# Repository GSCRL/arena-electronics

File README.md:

# arena-electronics

# Other Repos

UI / Webserver - https://github.com/fubarlabs/RobotCombatOverlay
ESP32 Firmware - https://github.com/GSCRL/bot-arena-control
## Build Arg Notes

```ini
check_skip_packages = yes
lib_deps = bblanchon/ArduinoJson
build_flags = -O2 -D DEBUG_ESP_PORT=Serial
build_unflags = -Os
```

# Broker Setup

```
allow_anonymous true

listener 1883
protocol mqtt

listener 9001
protocol websockets
```

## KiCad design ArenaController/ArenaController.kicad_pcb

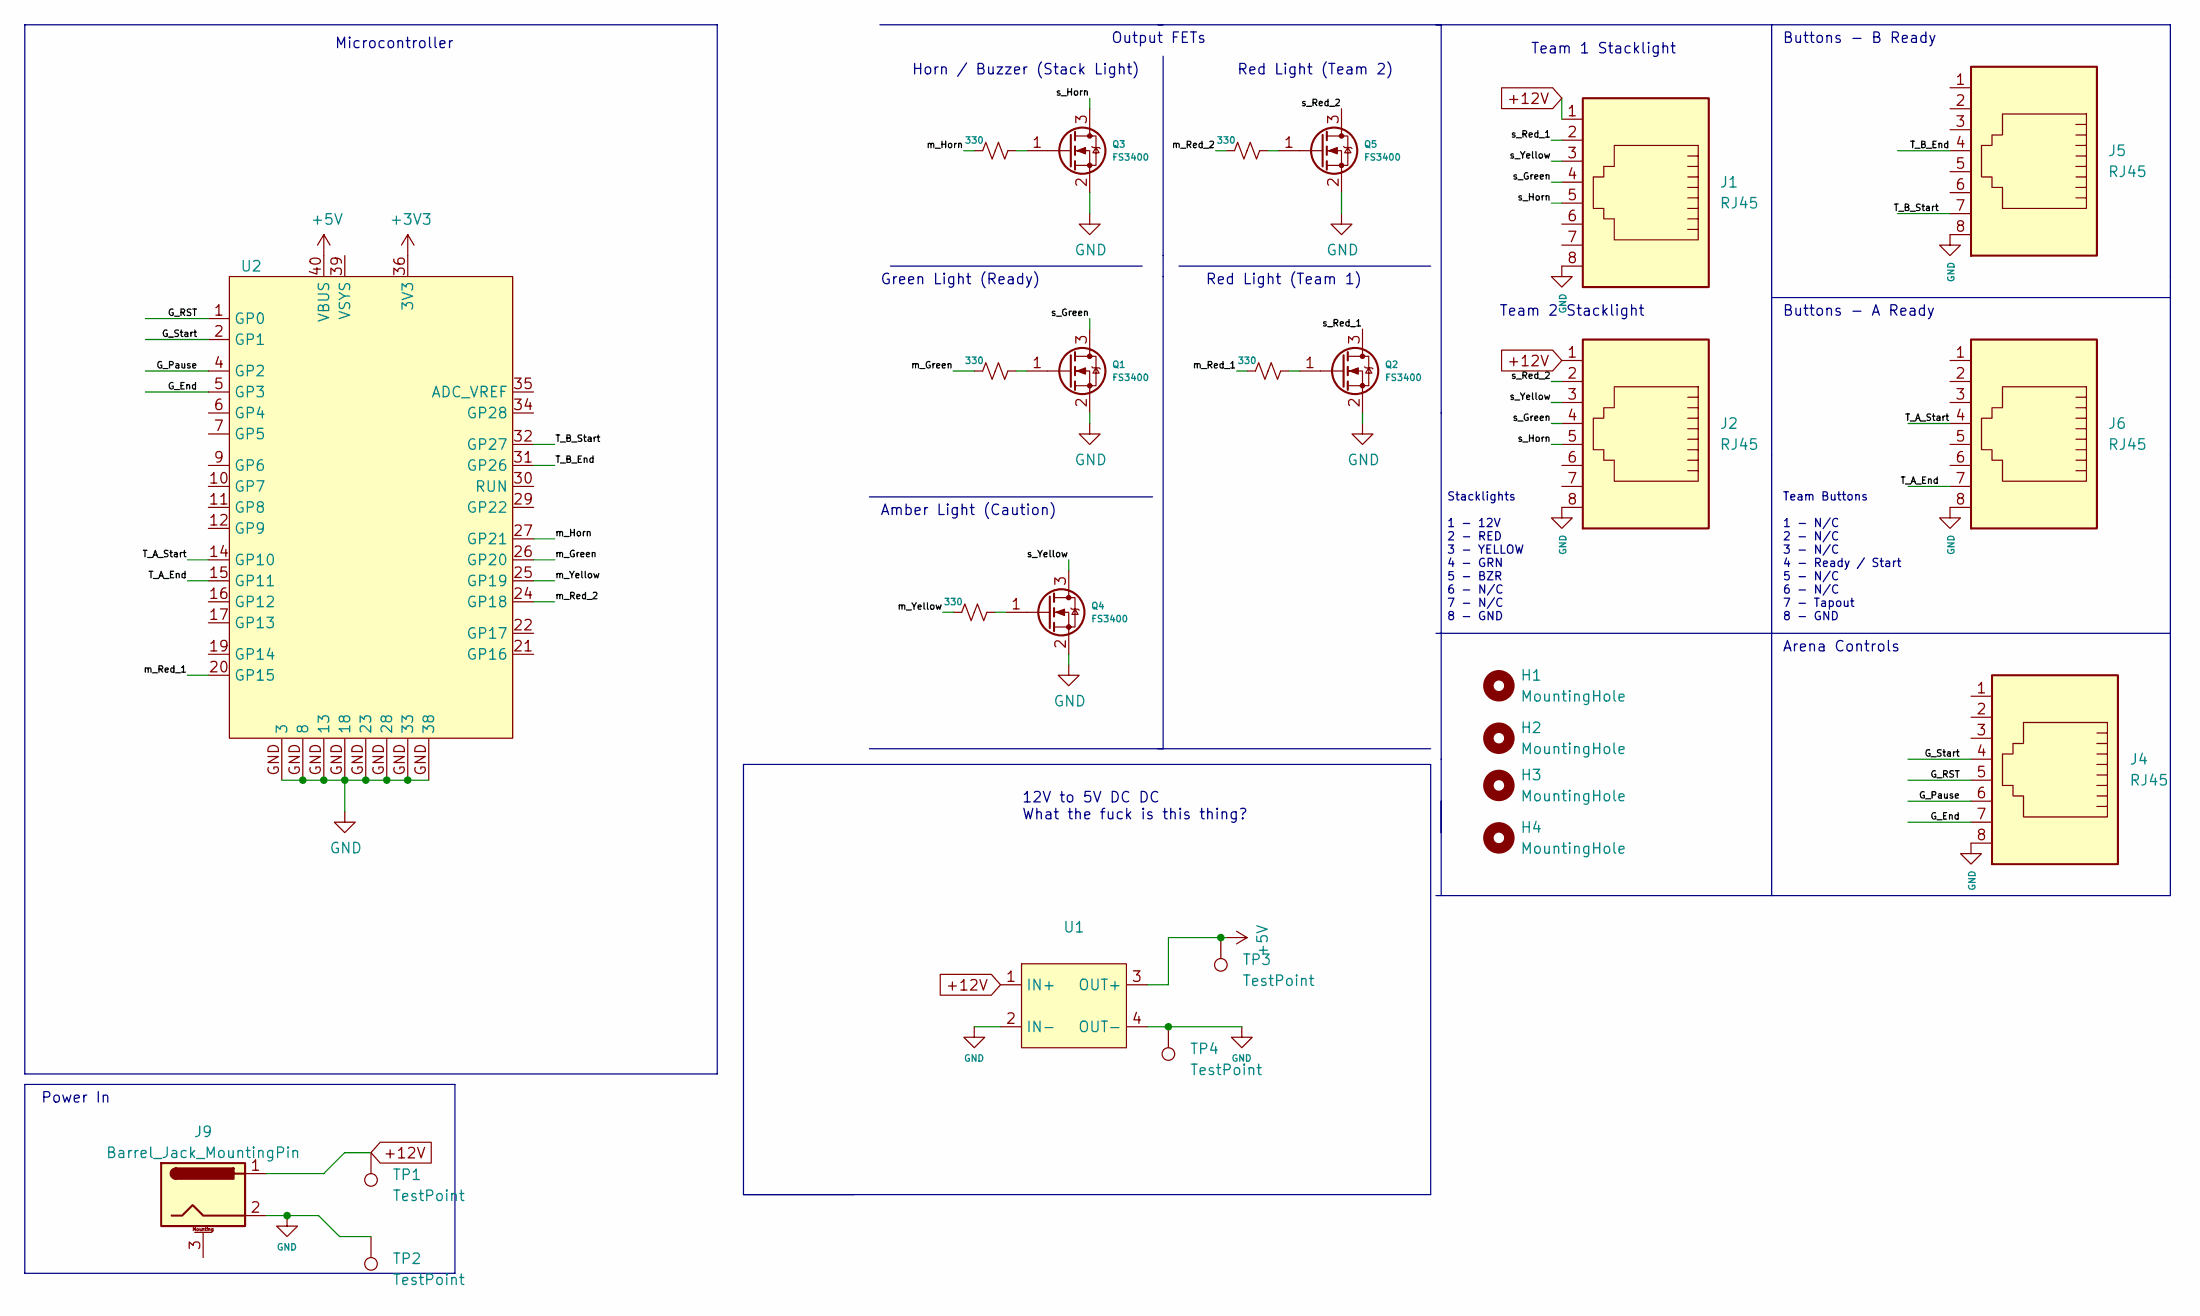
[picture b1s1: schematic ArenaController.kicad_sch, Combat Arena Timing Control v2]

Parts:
H1, H2, H3, H4: MountingHole; MountingHole_3.2mm_M3
J1, J2, J4, J5, J6: RJ45; RCH RC00139
J9: Barrel_Jack_MountingPin; BarrelJack_Horizontal
Q1, Q2, Q3, Q4, Q5: FS3400; SOT-23
R1, R2, R3, R4, R5: 330; R_1206_3216Metric_Pad1.30x1.75mm_HandSolder
TP1, TP2, TP3, TP4: TestPoint; TestPoint_Loop_D1.80mm_Drill1.0mm_Beaded
U1: LM2596_Module
U2: Raspberry_Pi_Pico_SMT_THT

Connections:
+3V3: U2.36 (3V3)
+5V: TP3.1, U1.3 (OUT+), U2.40 (VBUS)
+12V: J1.1, J2.1, J9.1, TP1.1, U1.1 (IN+)
/G_End: J4.7, U2.5 (GP3)
/G_Pause: J4.6, U2.4 (GP2)
/G_RST: J4.5, U2.1 (GP0)
/G_Start: J4.4, U2.2 (GP1)
/T_A_End: J6.7, U2.15 (GP11)
/T_A_Start: J6.4, U2.14 (GP10)
/T_B_End: J5.4, U2.31 (GP26)
/T_B_Start: J5.7, U2.32 (GP27)
/m_Green: R1.2, U2.26 (GP20)
/m_Horn: R2.2, U2.27 (GP21)
/m_Red_1: R5.2, U2.20 (GP15)
/m_Red_2: R4.2, U2.24 (GP18)
/m_Yellow: R3.2, U2.25 (GP19)
/s_Green: J1.4, J2.4, Q1.3 (D)
/s_Horn: J1.5, J2.5, Q3.3 (D)
/s_Red_1: J1.2, Q2.3 (D)
/s_Red_2: J2.2, Q5.3 (D)
/s_Yellow: J1.3, J2.3, Q4.3 (D)
GND: J1.8, J2.8, J4.8, J5.8, J6.8, J9.2, Q1.2 (S), Q2.2 (S), Q3.2 (S), Q4.2 (S), Q5.2 (S), TP2.1, TP4.1, U1.2 (IN-), U1.4 (OUT-), U2.GND (13)
unnamed: Q1.1 (G), R1.1
unnamed: Q2.1 (G), R5.1
unnamed: Q3.1 (G), R2.1
unnamed: Q4.1 (G), R3.1
unnamed: Q5.1 (G), R4.1

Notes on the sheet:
Amber Light (Caution)
Arena Controls
Microcontroller
Green Light (Ready)
Buttons - A Ready
Team 2 Stacklight
12V to 5V DC DC What the fuck is this thing?
Power In
Team 1 Stacklight
Output FETs
Horn / Buzzer (Stack Light)
Team Buttons 1 - N/C 2 - N/C 3 - N/C 4 - Ready / Start 5 - N/C 6 - N/C 7 - Tapout 8 - GND
Buttons - B Ready
Red Light (Team 1)
Red Light (Team 2)
Stacklights 1 - 12V 2 - RED 3 - YELLOW 4 - GRN 5 - BZR 6 - N/C 7 - N/C 8 - GND

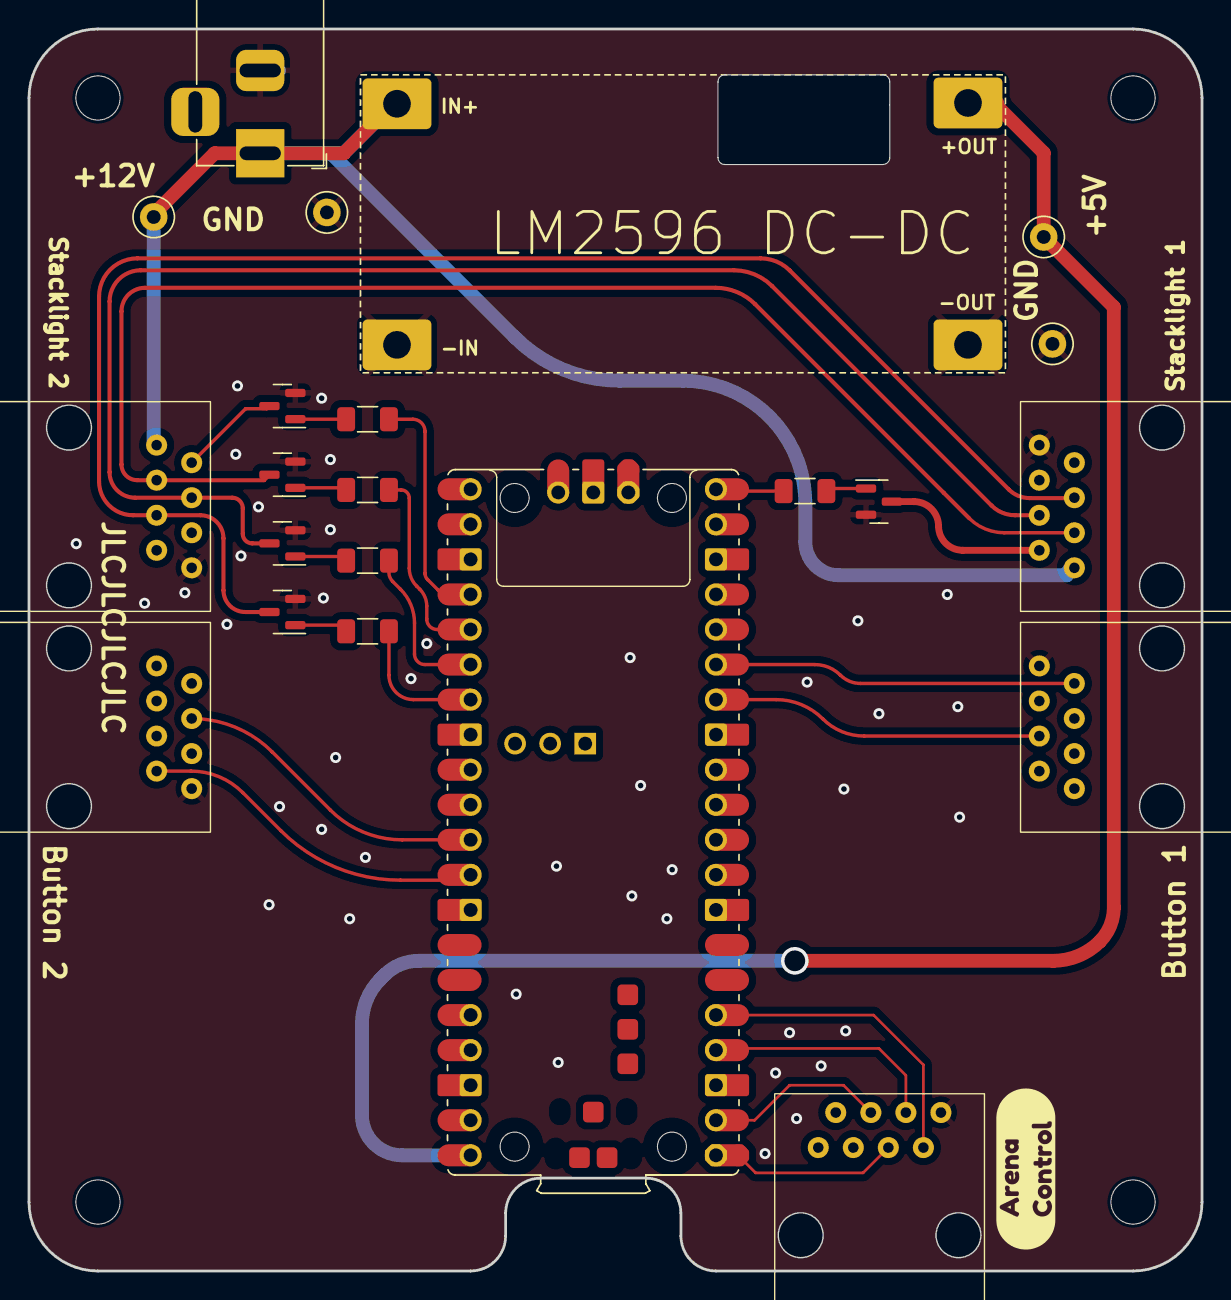
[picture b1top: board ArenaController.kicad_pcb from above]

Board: 2 copper layers, 85.0 x 90.0 mm, 27 parts (0 on the bottom side), 26 nets.

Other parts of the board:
kibuzzard-638A219C: G***; kibuzzard-638A219C

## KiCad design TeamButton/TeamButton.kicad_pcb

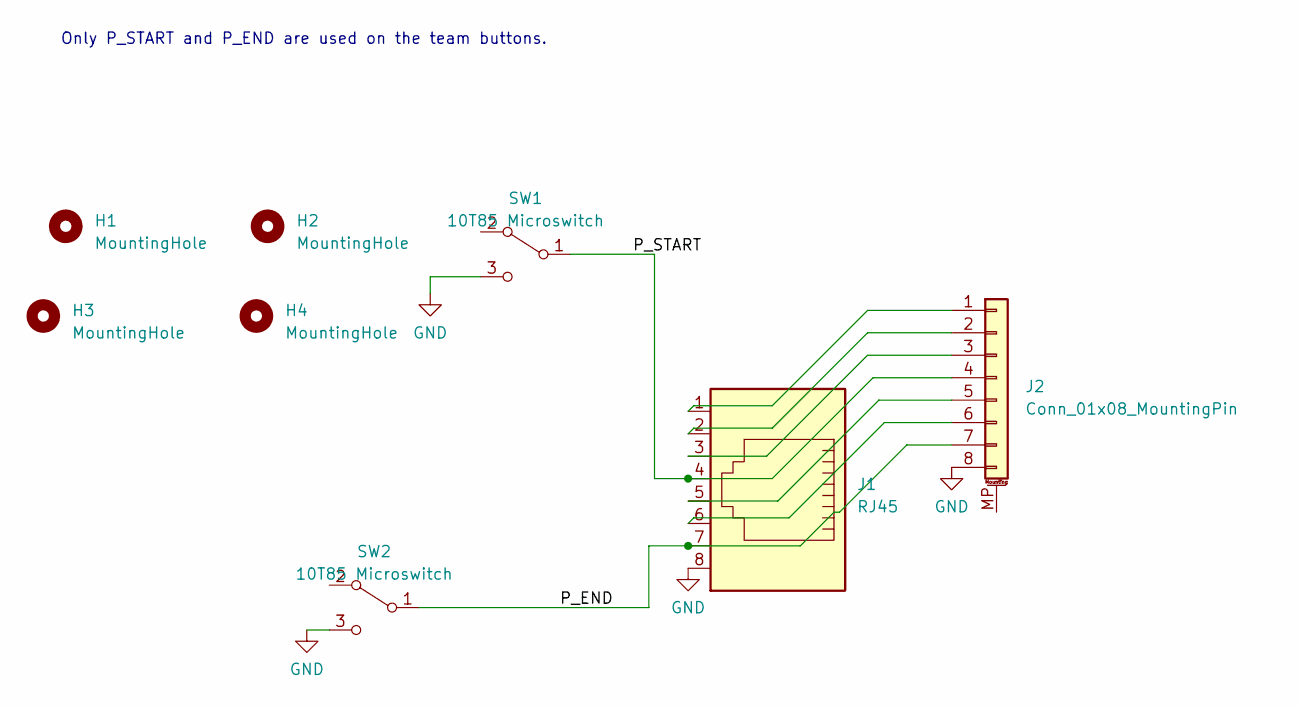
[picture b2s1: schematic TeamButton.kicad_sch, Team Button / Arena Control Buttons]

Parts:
H1, H2, H3, H4: MountingHole; MountingHole_3.2mm_M3
J1: RJ45; RCH RC00139
J2: Conn_01x08_MountingPin; PinSocket_1x08_P2.54mm_Horizontal
SW1, SW2: 10T85 Microswitch; 10T85 Microswitch with M3 mounts

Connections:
/P_END: J1.7, J2.7, SW2.1 (C)
/P_START: J1.4, J2.4, SW1.1 (C)
GND: J1.8, J2.8, SW1.3 (NO), SW2.3 (NO)
unnamed: J1.1, J2.1
unnamed: J1.2, J2.2
unnamed: J1.3, J2.3
unnamed: J1.5, J2.5
unnamed: J1.6, J2.6

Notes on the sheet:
Only P_START and P_END are used on the team buttons.

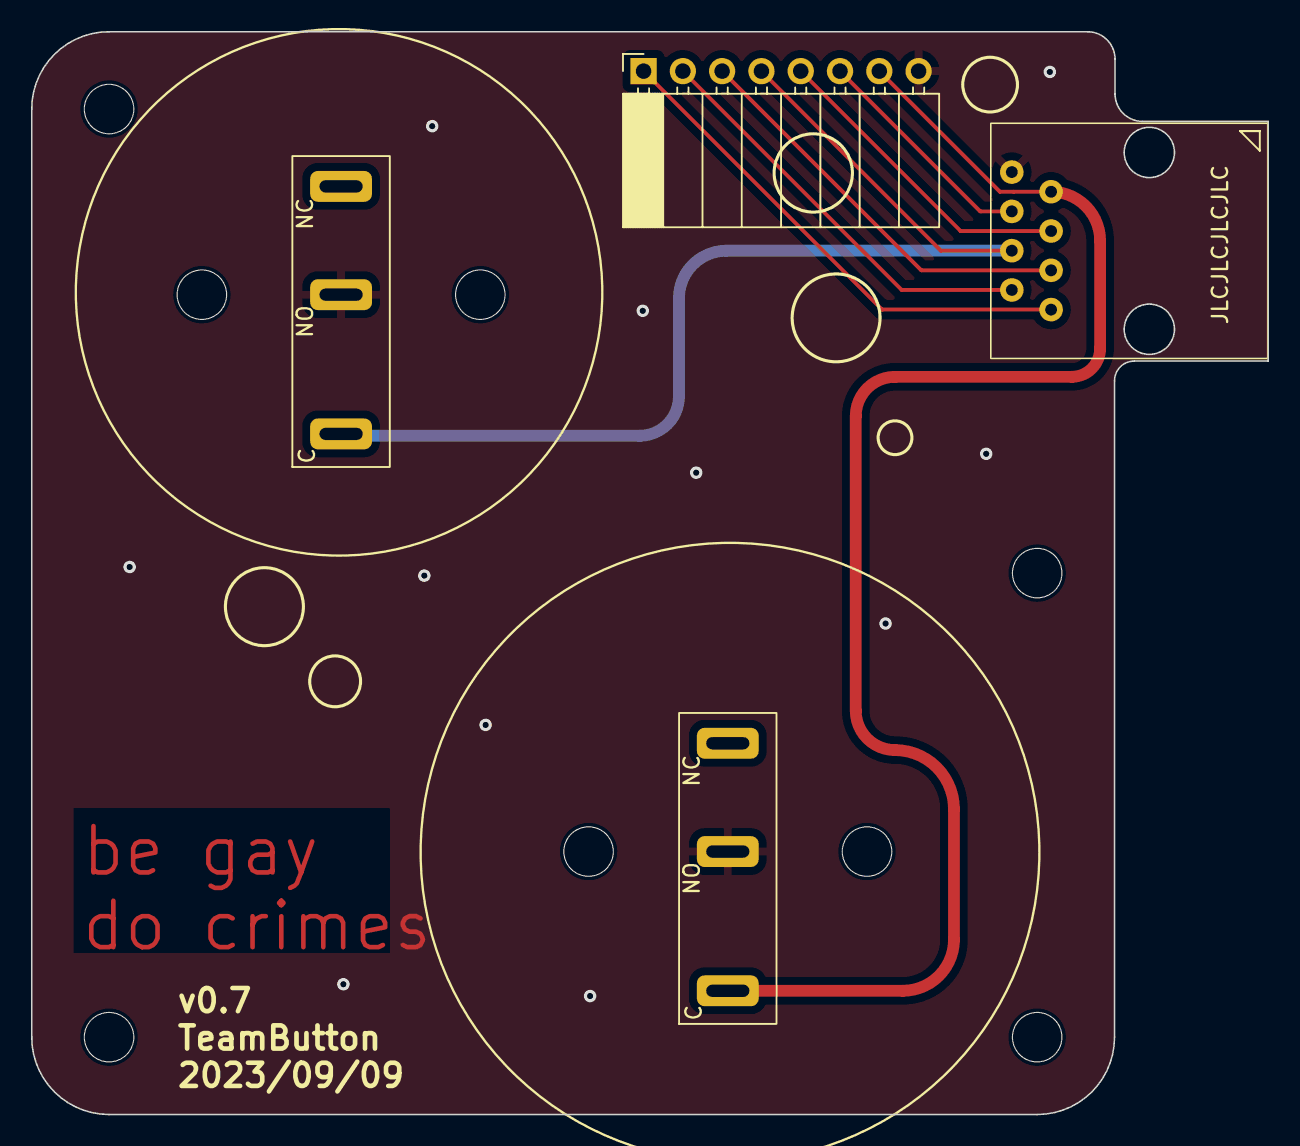
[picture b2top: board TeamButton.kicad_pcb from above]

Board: 2 copper layers, 79.9 x 70.0 mm, 8 parts (0 on the bottom side), 8 nets.

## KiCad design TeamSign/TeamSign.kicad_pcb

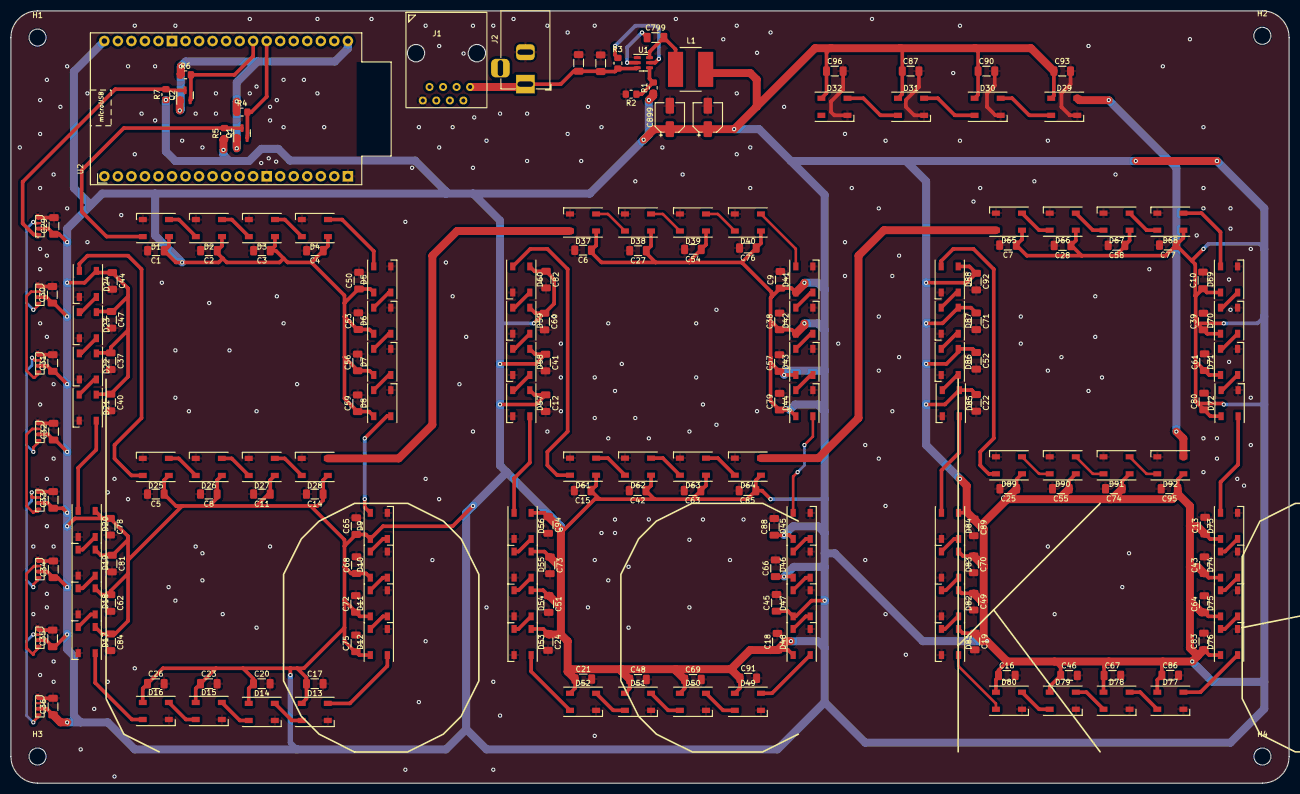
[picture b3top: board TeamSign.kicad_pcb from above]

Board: 2 copper layers, 240.0 x 145.0 mm, 215 parts (0 on the bottom side), 106 nets.

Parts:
C1, C2, C3, C4, C5, C6, C7, C8, C9, C10, C11, C12, C13, C14, C15, C16, C17, C18, C19, C20, C21, C22, C23, C24, C25, C26, C27, C28, C29, C30, C31, C32, C33, C34, C35, C36, C37, C38, C39, C40, C41, C42, C43, C44, C45, C46, C47, C48, C49, C50, C51, C52, C53, C54, C55, C56, C57, C58, C59, C60, C61, C62, C63, C64, C65, C66, C67, C68, C69, C70, C71, C72, C73, C74, C75, C76, C77, C78, C79, C80, C81, C82, C83, C84, C85, C86, C87, C88, C89, C90, C91, C92, C93, C94, C95, C96, C799: 100nF; C_1206_3216Metric_Pad1.33x1.80mm_HandSolder
C898, C899: 22uF; CP_Elec_5x5.4
C998, C999: 10uF; C_1206_3216Metric_Pad1.33x1.80mm_HandSolder
D1, D2, D3, D4, D5, D6, D7, D8, D9, D10, D11, D12, D13, D14, D15, D16, D17, D18, D19, D20, D21, D22, D23, D24, D25, D26, D27, D28, D29, D30, D31, D32, D37, D38, D39, D40, D41, D42, D43, D44, D45, D46, D47, D48, D49, D50, D51, D52, D53, D54, D55, D56, D57, D58, D59, D60, D61, D62, D63, D64, D65, D66, D67, D68, D69, D70, D71, D72, D73, D74, D75, D76, D77, D78, D79, D80, D81, D82, D83, D84, D85, D86, D87, D88, D89, D90, D91, D92: SK6812; LED_SK6812_PLCC4_5.0x5.0mm_P3.2mm
D300, D301, D302, D303, D304, D305, D306, D307: SK6812-Side-A
H1, H2, H3, H4: MountingHole; MountingHole_3.2mm_M3
J1: RJ45; RCH RC00139
J2: Barrel_Jack_MountingPin; BarrelJack_Horizontal
L1: 3.3uH; L_Bourns_SRN8040TA
Q1, Q2: BSS138; SOT-23
R1: 54.9kΩ; R_0805_2012Metric_Pad1.20x1.40mm_HandSolder
R2, R3, R4, R5, R6, R7: 10kΩ; R_0805_2012Metric_Pad1.20x1.40mm_HandSolder
U1: TPS563200; SOT-23-6
U2: ESP32-Devkit_C_V4; MODULE_ESP32_DEVKIT_C_V4

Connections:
+3.3V: Q1.1 (G), Q2.1 (G), R4.1, R6.1, U2.20 (3.3v)
+5V: C1.1, C2.1, C3.1, C4.1, C5.1, C6.1, C7.1, C8.1, C9.1, C10.1, C11.1, C12.1, C13.1, C14.1, C15.1, C16.1, C17.1, C18.1, C19.1, C20.1, C21.1, C22.1, C23.1, C24.1, C25.1, C26.1, C27.1, C28.1, C29.1, C30.1, C31.1, C32.1, C33.1, C34.1, C35.1, C36.1, C37.1, C38.1, C39.1, C40.1, C41.1, C42.1, C43.1, C44.1, C45.1, C46.1, C47.1, C48.1, C49.1, C50.1, C51.1, C52.1, C53.1, C54.1, C55.1, C56.1, C57.1, C58.1, C59.1, C60.1, C61.1, C62.1, C63.1, C64.1, C65.1, C66.1, C67.1, C68.1, C69.1, C70.1, C71.1, C72.1, C73.1, C74.1, C75.1, C76.1, C77.1, C78.1, C79.1, C80.1, C81.1, C82.1, C83.1, C84.1, C85.1, C86.1, C87.1, C88.1, C89.1, C90.1, C91.1, C92.1, C93.1, C94.1, C95.1, C96.1, C898.1, C899.1, D1.3 (VDD), D2.3 (VDD), D3.3 (VDD), D4.3 (VDD), D5.3 (VDD), D6.3 (VDD), D7.3 (VDD), D8.3 (VDD), D9.3 (VDD), D10.3 (VDD), D11.3 (VDD), D12.3 (VDD), D13.3 (VDD), D14.3 (VDD), D15.3 (VDD), D16.3 (VDD), D17.3 (VDD), D18.3 (VDD), D19.3 (VDD), D20.3 (VDD), D21.3 (VDD), D22.3 (VDD), D23.3 (VDD), D24.3 (VDD), D25.3 (VDD), D26.3 (VDD), D27.3 (VDD), D28.3 (VDD), D29.3 (VDD), D30.3 (VDD), D31.3 (VDD), D32.3 (VDD), D37.3 (VDD), D38.3 (VDD), D39.3 (VDD), D40.3 (VDD), D41.3 (VDD), D42.3 (VDD), D43.3 (VDD), D44.3 (VDD), D45.3 (VDD), D46.3 (VDD), D47.3 (VDD), D48.3 (VDD), D49.3 (VDD), D50.3 (VDD), D51.3 (VDD), D52.3 (VDD), D53.3 (VDD), D54.3 (VDD), D55.3 (VDD), D56.3 (VDD), D57.3 (VDD), D58.3 (VDD), D59.3 (VDD), D60.3 (VDD), D61.3 (VDD), D62.3 (VDD), D63.3 (VDD), D64.3 (VDD), D65.3 (VDD), D66.3 (VDD), D67.3 (VDD), D68.3 (VDD), D69.3 (VDD), D70.3 (VDD), D71.3 (VDD), D72.3 (VDD), D73.3 (VDD), D74.3 (VDD), D75.3 (VDD), D76.3 (VDD), D77.3 (VDD), D78.3 (VDD), D79.3 (VDD), D80.3 (VDD), D81.3 (VDD), D82.3 (VDD), D83.3 (VDD), D84.3 (VDD), D85.3 (VDD), D86.3 (VDD), D87.3 (VDD), D88.3 (VDD), D89.3 (VDD), D90.3 (VDD), D91.3 (VDD), D92.3 (VDD), D300.2 (VDD), D301.2 (VDD), D302.2 (VDD), D303.2 (VDD), D304.2 (VDD), D305.2 (VDD), D306.2 (VDD), D307.2 (VDD), L1.2, R1.1, R5.1, R7.1, U2.38 (5V)
+12V: C998.1, C999.1, J1.1, J2.1, R3.1, U1.3 (VIN)
/LED Array 1/sk_output_pin: D28.4 (DOUT), D37.2 (DIN)
/LED Array 1/sk_pin1: D12.4 (DOUT), D13.2 (DIN)
/LED Array 1/sk_pin2: D25.4 (DOUT), D26.2 (DIN)
/LED Array 2/sk_output_pin: D64.4 (DOUT), D65.2 (DIN)
/LED Array 2/sk_pin1: D48.4 (DOUT), D49.2 (DIN)
/LED Array 2/sk_pin2: D61.4 (DOUT), D62.2 (DIN)
/LED Array 3/sk_pin1: D76.4 (DOUT), D77.2 (DIN)
/LED Array 3/sk_pin2: D89.4 (DOUT), D90.2 (DIN)
/led_output_frontfiring: D29.2 (DIN), D92.4 (DOUT)
/sk_input: Q1.2 (S), R4.2, U2.26 (RTC_GPIO9/XTal32P/Touch9/ADC1_4/GPIO32)
/sk_lvl_shifted: D1.2 (DIN), Q1.3 (D), R5.2
/stacklight_lvl_shift: D300.1 (DIN), Q2.3 (D), R7.2
/stacklight_out: Q2.2 (S), R6.2, U2.27 (RTC_GPIO8/Xtal32N/Touch8/ADC1_5/GPIO33)
GND: C1.2, C2.2, C3.2, C4.2, C5.2, C6.2, C7.2, C8.2, C9.2, C10.2, C11.2, C12.2, C13.2, C14.2, C15.2, C16.2, C17.2, C18.2, C19.2, C20.2, C21.2, C22.2, C23.2, C24.2, C25.2, C26.2, C27.2, C28.2, C29.2, C30.2, C31.2, C32.2, C33.2, C34.2, C35.2, C36.2, C37.2, C38.2, C39.2, C40.2, C41.2, C42.2, C43.2, C44.2, C45.2, C46.2, C47.2, C48.2, C49.2, C50.2, C51.2, C52.2, C53.2, C54.2, C55.2, C56.2, C57.2, C58.2, C59.2, C60.2, C61.2, C62.2, C63.2, C64.2, C65.2, C66.2, C67.2, C68.2, C69.2, C70.2, C71.2, C72.2, C73.2, C74.2, C75.2, C76.2, C77.2, C78.2, C79.2, C80.2, C81.2, C82.2, C83.2, C84.2, C85.2, C86.2, C87.2, C88.2, C89.2, C90.2, C91.2, C92.2, C93.2, C94.2, C95.2, C96.2, C898.2, C899.2, C998.2, C999.2, D1.1 (VSS), D2.1 (VSS), D3.1 (VSS), D4.1 (VSS), D5.1 (VSS), D6.1 (VSS), D7.1 (VSS), D8.1 (VSS), D9.1 (VSS), D10.1 (VSS), D11.1 (VSS), D12.1 (VSS), D13.1 (VSS), D14.1 (VSS), D15.1 (VSS), D16.1 (VSS), D17.1 (VSS), D18.1 (VSS), D19.1 (VSS), D20.1 (VSS), D21.1 (VSS), D22.1 (VSS), D23.1 (VSS), D24.1 (VSS), D25.1 (VSS), D26.1 (VSS), D27.1 (VSS), D28.1 (VSS), D29.1 (VSS), D30.1 (VSS), D31.1 (VSS), D32.1 (VSS), D37.1 (VSS), D38.1 (VSS), D39.1 (VSS), D40.1 (VSS), D41.1 (VSS), D42.1 (VSS), D43.1 (VSS), D44.1 (VSS), D45.1 (VSS), D46.1 (VSS), D47.1 (VSS), D48.1 (VSS), D49.1 (VSS), D50.1 (VSS), D51.1 (VSS), D52.1 (VSS), D53.1 (VSS), D54.1 (VSS), D55.1 (VSS), D56.1 (VSS), D57.1 (VSS), D58.1 (VSS), D59.1 (VSS), D60.1 (VSS), D61.1 (VSS), D62.1 (VSS), D63.1 (VSS), D64.1 (VSS), D65.1 (VSS), D66.1 (VSS), D67.1 (VSS), D68.1 (VSS), D69.1 (VSS), D70.1 (VSS), D71.1 (VSS), D72.1 (VSS), D73.1 (VSS), D74.1 (VSS), D75.1 (VSS), D76.1 (VSS), D77.1 (VSS), D78.1 (VSS), D79.1 (VSS), D80.1 (VSS), D81.1 (VSS), D82.1 (VSS), D83.1 (VSS), D84.1 (VSS), D85.1 (VSS), D86.1 (VSS), D87.1 (VSS), D88.1 (VSS), D89.1 (VSS), D90.1 (VSS), D91.1 (VSS), D92.1 (VSS), D300.4 (GND), D301.4 (GND), D302.4 (GND), D303.4 (GND), D304.4 (GND), D305.4 (GND), D306.4 (GND), D307.4 (GND), J1.8, J2.2, R2.2, U1.1 (GND), U2.13 (GND), U2.19 (GND), U2.33 (GND)
unnamed: D1.4 (DOUT), D2.2 (DIN)
unnamed: D2.4 (DOUT), D3.2 (DIN)
unnamed: D3.4 (DOUT), D4.2 (DIN)
unnamed: D4.4 (DOUT), D5.2 (DIN)
unnamed: D5.4 (DOUT), D6.2 (DIN)
unnamed: D6.4 (DOUT), D7.2 (DIN)
unnamed: D7.4 (DOUT), D8.2 (DIN)
unnamed: D8.4 (DOUT), D9.2 (DIN)
unnamed: D9.4 (DOUT), D10.2 (DIN)
unnamed: D10.4 (DOUT), D11.2 (DIN)
unnamed: D11.4 (DOUT), D12.2 (DIN)
unnamed: D13.4 (DOUT), D14.2 (DIN)
unnamed: D14.4 (DOUT), D15.2 (DIN)
unnamed: D15.4 (DOUT), D16.2 (DIN)
unnamed: D16.4 (DOUT), D17.2 (DIN)
unnamed: D17.4 (DOUT), D18.2 (DIN)
unnamed: D18.4 (DOUT), D19.2 (DIN)
unnamed: D19.4 (DOUT), D20.2 (DIN)
unnamed: D20.4 (DOUT), D21.2 (DIN)
unnamed: D21.4 (DOUT), D22.2 (DIN)
unnamed: D22.4 (DOUT), D23.2 (DIN)
unnamed: D23.4 (DOUT), D24.2 (DIN)
unnamed: D24.4 (DOUT), D25.2 (DIN)
unnamed: D26.4 (DOUT), D27.2 (DIN)
unnamed: D27.4 (DOUT), D28.2 (DIN)
unnamed: D29.4 (DOUT), D30.2 (DIN)
unnamed: D30.4 (DOUT), D31.2 (DIN)
unnamed: D31.4 (DOUT), D32.2 (DIN)
unnamed: D37.4 (DOUT), D38.2 (DIN)
unnamed: D38.4 (DOUT), D39.2 (DIN)
unnamed: D39.4 (DOUT), D40.2 (DIN)
unnamed: D40.4 (DOUT), D41.2 (DIN)
unnamed: D41.4 (DOUT), D42.2 (DIN)
unnamed: D42.4 (DOUT), D43.2 (DIN)
unnamed: D43.4 (DOUT), D44.2 (DIN)
unnamed: D44.4 (DOUT), D45.2 (DIN)
unnamed: D45.4 (DOUT), D46.2 (DIN)
unnamed: D46.4 (DOUT), D47.2 (DIN)
unnamed: D47.4 (DOUT), D48.2 (DIN)
unnamed: D49.4 (DOUT), D50.2 (DIN)
unnamed: D50.4 (DOUT), D51.2 (DIN)
unnamed: D51.4 (DOUT), D52.2 (DIN)
unnamed: D52.4 (DOUT), D53.2 (DIN)
unnamed: D53.4 (DOUT), D54.2 (DIN)
unnamed: D54.4 (DOUT), D55.2 (DIN)
unnamed: D55.4 (DOUT), D56.2 (DIN)
unnamed: D56.4 (DOUT), D57.2 (DIN)
unnamed: D57.4 (DOUT), D58.2 (DIN)
unnamed: D58.4 (DOUT), D59.2 (DIN)
unnamed: D59.4 (DOUT), D60.2 (DIN)
unnamed: D60.4 (DOUT), D61.2 (DIN)
unnamed: D62.4 (DOUT), D63.2 (DIN)
unnamed: D63.4 (DOUT), D64.2 (DIN)
unnamed: D65.4 (DOUT), D66.2 (DIN)
unnamed: D66.4 (DOUT), D67.2 (DIN)
unnamed: D67.4 (DOUT), D68.2 (DIN)
unnamed: D68.4 (DOUT), D69.2 (DIN)
unnamed: D69.4 (DOUT), D70.2 (DIN)
unnamed: D70.4 (DOUT), D71.2 (DIN)
unnamed: D71.4 (DOUT), D72.2 (DIN)
unnamed: D72.4 (DOUT), D73.2 (DIN)
unnamed: D73.4 (DOUT), D74.2 (DIN)
unnamed: D74.4 (DOUT), D75.2 (DIN)
unnamed: D75.4 (DOUT), D76.2 (DIN)
unnamed: D77.4 (DOUT), D78.2 (DIN)
unnamed: D78.4 (DOUT), D79.2 (DIN)
unnamed: D79.4 (DOUT), D80.2 (DIN)
unnamed: D80.4 (DOUT), D81.2 (DIN)
unnamed: D81.4 (DOUT), D82.2 (DIN)
unnamed: D82.4 (DOUT), D83.2 (DIN)
unnamed: D83.4 (DOUT), D84.2 (DIN)
unnamed: D84.4 (DOUT), D85.2 (DIN)
unnamed: D85.4 (DOUT), D86.2 (DIN)
unnamed: D86.4 (DOUT), D87.2 (DIN)
unnamed: D87.4 (DOUT), D88.2 (DIN)
unnamed: D88.4 (DOUT), D89.2 (DIN)
unnamed: D90.4 (DOUT), D91.2 (DIN)
unnamed: D91.4 (DOUT), D92.2 (DIN)
unnamed: D300.3 (DOUT), D301.1 (DIN)
unnamed: D301.3 (DOUT), D302.1 (DIN)
unnamed: D302.3 (DOUT), D303.1 (DIN)
unnamed: D303.3 (DOUT), D304.1 (DIN)
unnamed: D304.3 (DOUT), D305.1 (DIN)
unnamed: D305.3 (DOUT), D306.1 (DIN)
unnamed: D306.3 (DOUT), D307.1 (DIN)
unnamed: R3.2, U1.5 (EN)
unnamed: C799.1, U1.2 (SW)
unnamed: C799.2, L1.1, U1.6 (VBST)
unnamed: R1.2, R2.1, U1.4 (VFB)

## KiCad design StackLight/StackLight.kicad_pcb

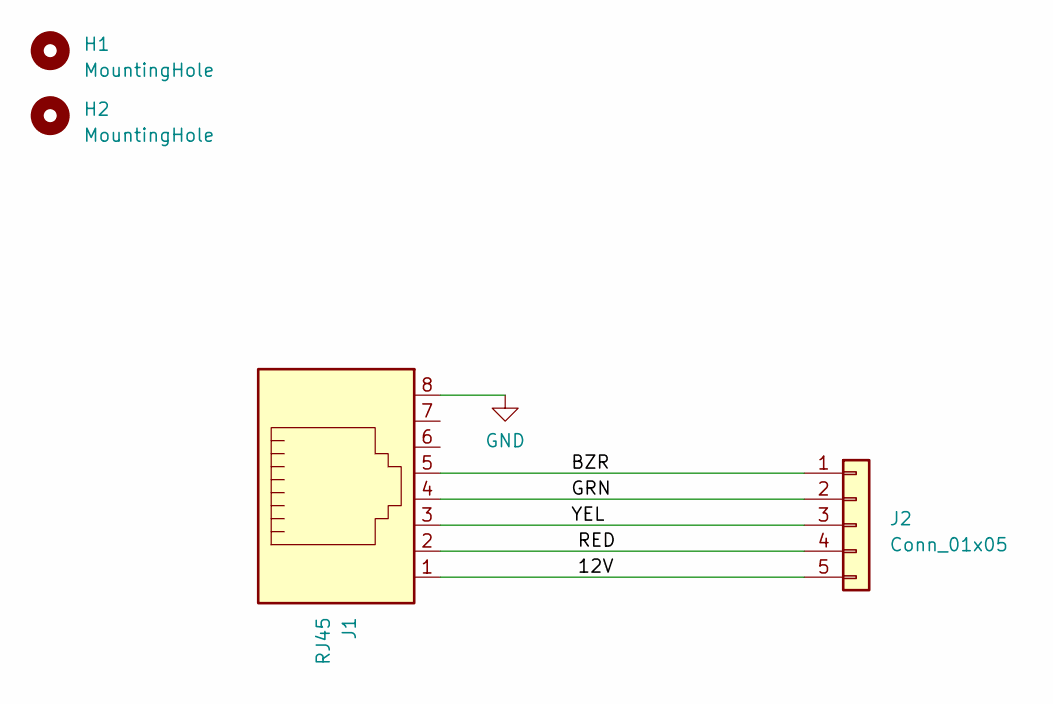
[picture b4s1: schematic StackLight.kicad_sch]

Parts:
H1, H2: MountingHole; MountingHole_3.2mm_M3
J1: RJ45; RCH RC00139
J2: Conn_01x05; SolderWire-1.5sqmm_1x05_P6mm_D1.7mm_OD3mm_Relief

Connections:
/12V: J1.1, J2.5
/BZR: J1.5, J2.1
/GRN: J1.4, J2.2
/RED: J1.2, J2.4
/YEL: J1.3, J2.3
GND: J1.8

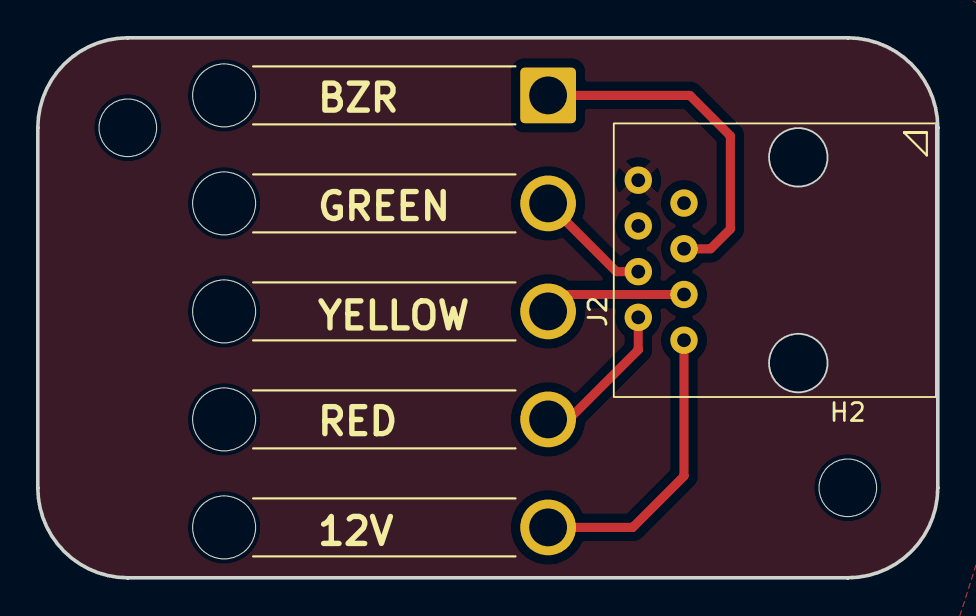
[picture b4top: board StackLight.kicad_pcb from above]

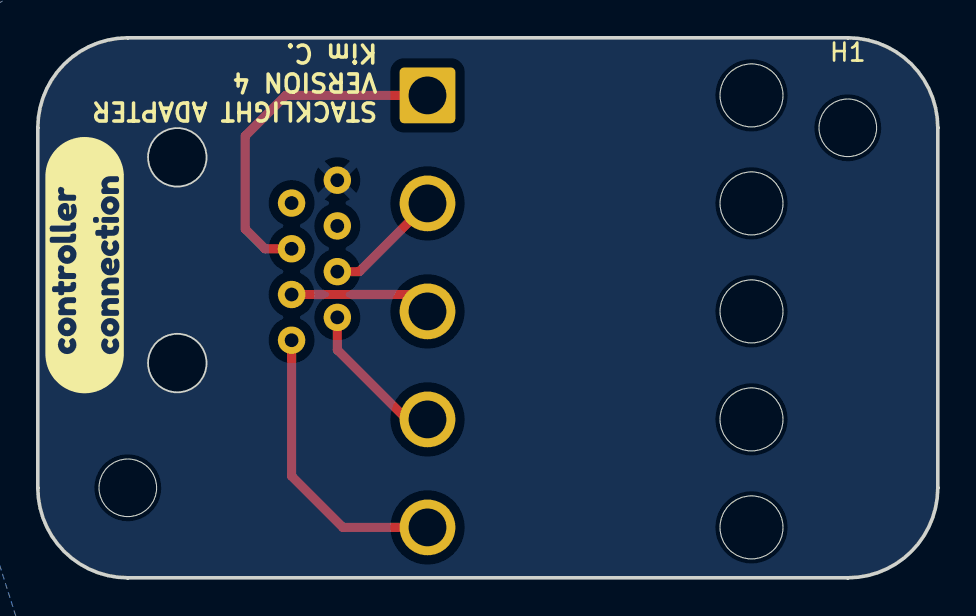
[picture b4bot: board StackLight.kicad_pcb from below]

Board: 2 copper layers, 50.0 x 30.0 mm, 5 parts (2 on the bottom side), 5 nets.

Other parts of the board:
kibuzzard-631545B4: G***; kibuzzard-631545B4

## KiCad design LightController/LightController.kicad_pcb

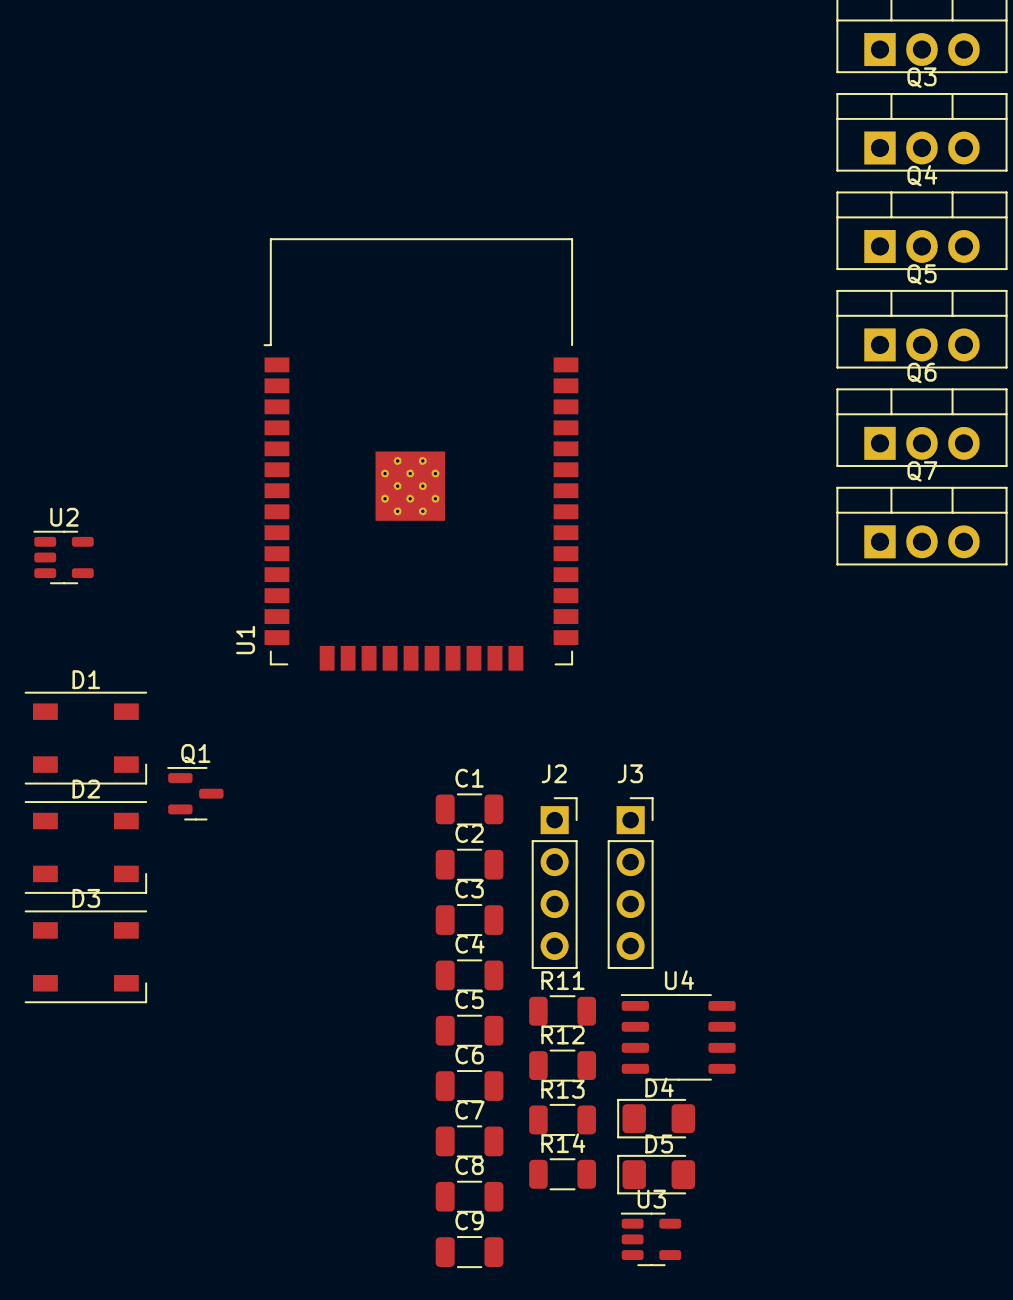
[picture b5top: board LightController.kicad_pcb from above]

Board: 2 copper layers, 31 parts (0 on the bottom side), 22 nets, no tracks yet.

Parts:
C1, C2, C3: C; C_1206_3216Metric
C4, C6: u1F; C_1206_3216Metric
C5, C7: 1uF; C_1206_3216Metric
C8: 10uF; C_1206_3216Metric
C9: .1uF; C_1206_3216Metric
D1, D2, D3: SK6812; LED_SK6812_PLCC4_5.0x5.0mm_P3.2mm
D4, D5: D; D_1206_3216Metric_Pad1.42x1.75mm_HandSolder
J2, J3: Conn_01x04; PinSocket_1x04_P2.54mm_Vertical
Q1: BSS138; SOT-23
Q2, Q3, Q4, Q5, Q6, Q7: Q_NMOS_GDS; TO-220-3_Vertical
R11: 110ohm; R_1206_3216Metric
R12: 330ohm; R_1206_3216Metric
R13: 330 ohm; R_1206_3216Metric
R14: 200 ohm; R_1206_3216Metric
U1: ESP32-WROOM-32D; ESP32-WROOM-32
U2, U3: AP3012; SOT-23-5
U4: MAX485E; SOP-8_3.9x4.9mm_P1.27mm

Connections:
/3v3: C8.1, C9.1, Q1.1 (G), U1.2 (VDD), U4.2 (~RE), U4.3 (DE), U4.8 (VCC)
/5V: C1.2, C2.2, C3.2, C5.2, D1.3 (VDD), D2.3 (VDD), D3.3 (VDD), D4.1 (K), R12.2
/12V: C4.1, C7.2, D5.1 (K), J2.1, J3.1, R13.2, U2.4 (~SHDN), U2.5 (IN)
/LED_DATA_PIN: D1.2 (DIN), Q1.3 (D)
/RS485_A: U1.27 (IO16), U4.1 (RO)
/RS485_B: U1.28 (IO17), U4.4 (DI)
/SD_RESERVED: U1.13 (IO14), U1.14 (IO12), U1.16 (IO13), U1.23 (IO15), U1.24 (IO2), U1.26 (IO4)
/STATUS_LED: Q1.2 (S), U1.12 (IO27)
GND: C1.1, C2.1, C3.1, C4.2, C5.1, C6.2, C7.1, C8.2, C9.2, D1.1 (VSS), D2.1 (VSS), D3.1 (VSS), Q2.3 (S), Q3.3 (S), Q4.3 (S), Q5.3 (S), Q6.3 (S), Q7.3 (S), R11.1, R14.1, U1.1 (GND), U1.15 (GND), U1.38 (GND), U1.39 (GND), U2.2 (GND), U3.2 (GND), U4.5 (GND)
unnamed: D1.4 (DOUT), D2.2 (DIN)
unnamed: D2.4 (DOUT), D3.2 (DIN)
unnamed: D4.2 (A), U2.1 (SW)
unnamed: D5.2 (A), U3.1 (SW)
unnamed: J2.2, Q2.2 (D)
unnamed: J2.3, Q3.2 (D)
unnamed: J2.4, Q4.2 (D)
unnamed: J3.2, Q5.2 (D)
unnamed: J3.3, Q6.2 (D)
unnamed: J3.4, Q7.2 (D)
unnamed: R11.2, R12.1, U2.3 (FB)
unnamed: R13.1, R14.2, U3.3 (FB)
unnamed: C6.1, U3.4 (~SHDN), U3.5 (IN)

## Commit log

2022-12-16 initial project setup.
2022-12-24 Add the funky stuff to start. This will be hell btw.
2022-12-24 Updated first half of schematic, mostlyish. Lots to go for lighting.
2022-12-25 Update roughly, using the same schematic for the 3v3 and 5v stuff, still need to figure out values, etc.
2022-12-30 Add footprints and shit.
2023-01-26 Bring in old schematic for cleanup / base work.
2023-01-26 Update symbol libraries to have better barrel jack footprint. Yay!
2023-01-26 Update to shit.
2023-01-27 Updated ESP32 Cv4 footprint to include text label for microUSB, new line styles, etc. Still need to update the matched symbol.
2023-01-28 Added initial symbol for ESP32-DevkitCv4
2023-02-17 Add microswitch for start buttons.
2023-03-19 Added new files, swap to new FET for toggling, added FET as symbols.
2023-03-22 Added new DC DC symbol.
2023-03-22 Added more SMD nightmare parts.
2023-03-22 Swapped to ESP32 Devkit 4.
2023-03-22 Removed backups properly.
2023-03-24 initial add of DC DC footprint, will confirm with physical unit etc.
2023-03-24 Made empty PIO project for ESP32 code.
2023-03-27 small boardwork cleanup to try and lay it out.
2023-03-28 Started to organize board proper, did filled areas for 12V->5V input section.
2023-03-29 Updated layout, added major routing. Still need connector for the WS2812B output and pin relayout.
2023-03-30 Tiny cleanup, workable version, yay.
2023-03-31 Revision .4 layout with a sane ground plane, do fix the footprint shit tho
2023-04-05 Release v.4 for April event.
2023-04-12 PIO setup with Arduino framework, yay!
2023-04-12 Import old arena control code to get working basics, in theory. Verify pinouts, etc.
2023-04-12 Rename and added static analysis / checking tools.
2023-04-13 Updated team buttonboard to use M3 fasteners!
2023-04-14 Work day fixes for schematic, including re-polarizing the caps.
2023-04-14 Updated Button and Stacklight PCB to not have backwards fucking footprint shit.
2023-04-14 Added SPIFFS note for if we need to use embedded FS stuff. Yay!
2023-04-14 Update to non-hole design. Verify wire gagues.
2023-04-14 Added gay notations.
2023-04-14 Added spacer mounting holes to board in case are needed. Insert through back first. Use smaller fasteners, etc. Only one hole should be needed.
2023-04-14 Added visual flourish and confirmed microswitch locations.
2023-04-14 Same deal.
2023-04-14 Added wire strain relief that should fit.
2023-04-16 Basic webserver integration.
2023-04-16 Got build cache working to speed up test builds; yay!
2023-04-16 Added wssocket stuff to ecosystem and hopefully got it workable? Unclear atm.
2023-04-16 Changed back to WSPWSC v 2.3 as 2.3.6 has bugs.
2023-04-29 Update PCB errors and also remove software from this repo.
2023-04-29 Swap to a footprint with the correctly named pin in our project repo. Yay!
2023-05-04 Added initial teamsign and update symbol mistakes, mostly.
2023-05-04 Add team sign to gitignore and actually add stuff. Yay!
2023-05-04 Added links to current other repos to keep things cohesive.
2023-05-04 Update fp to include fixed keepouts for the THT part module.
2023-05-05 Initial footprint drag-in, add the svg, make the project libraries, and other stuff. Yay!
2023-05-05 Add SK6812-Side-A footprint/symbol to working area, as well as swapped to a stacklight connection that has a ground pin at the end for generic 12v power use. yay!
2023-05-06 Added subsheet for the other LEDs, still need to fix the capacitor footprint, but making solid progress it seems? Wild!
2023-05-06 Add PEM nut footprint starter to library, also did small tweaks to BOM and updated symbols to include the barrel jack antics. Yay!
2023-05-06 Shrink the labels for the side-firing SK6812SideAs, as well as start the footprint of the SMTSOM2.550BTR PEM nut.
2023-05-07 Place caps :)
2023-05-07 Added gerbers for TS to the ignore, plus added level shifting. Yay!
2023-05-07 Resolve subsheet antics... Yay.
2023-05-07 Placed so many capacitors, dear lord
2023-05-10 Added reset pins back in and broke out the pins in the team control area; should be easier now. Yay!
2023-05-10 Updated PCB revisions, swapped to larger footprint for stacklight connector, release cutting soon.
2023-05-10 Update repo to use consistent gerber outputs; yay!
2023-05-10 Made cut release script to automatically zip up PCBs for manufacture.
2023-05-10 Added power area, and started drawing pours.
2023-05-10 Fight with Freerouting, turns out there's a bug. Routing by hand.
2023-05-10 Mostly routed, needs side-firing cleanup.
2023-05-10 Changed thermal relief style, updated LEDs, seem to have worked? idk, yay
2023-05-11 Move connectors to front of board so they're in the bulky area.
2023-05-11 Updated link, BOM, and some general sanity changes.
2023-05-11 Add broker config to notes in README.
2023-05-12 Tiny PCB trace edits.
2023-05-12 added front PCB reference, experimental masking ig
2023-05-22 Update BOM + team sign PCB to not have diffuser issue.
2023-05-29 Add new inductor, add new chip resistor.
2023-05-29 chip thing etc
2023-06-06 Update ArenaController footprints to be over the edge and line up with the printed enclosure.
2023-06-07 Added Littelfuse TVS to the schematic.
2023-06-09 Update board to have less skullfscked routing and removed unused projects.
2023-06-19 Added test points and 3D model for pin headers to the ESP32 footprint.
2023-06-19 move power jack further right to permit complete enclosure for sealing sanity.
2023-06-24 Updated arena controls, delete team signs that are now deprecated, added more footprints.
2023-07-19 Release 7/19/23
2023-08-26 Changed output tool to fix missing drill files, at least in theory.
2023-08-27 Remove extraneous backup stuff.
2023-08-27 Update footprint library and also project to KiCAD 7.99 Nightly due to the properties pane making fixing the RP2040W footprint SO MUCH easier. Still verify, etc.
2023-08-27 Added RP2040W based arena controls.
2023-09-23 Fix footprint issue with the LM2596 and re-spin for next use.
2023-09-24 Update LM2596 to add THT cutout for potentiometer for adjustment, yay
2023-09-24 Tiny footprint keepout to hide THT pot adjustment for real this time.
